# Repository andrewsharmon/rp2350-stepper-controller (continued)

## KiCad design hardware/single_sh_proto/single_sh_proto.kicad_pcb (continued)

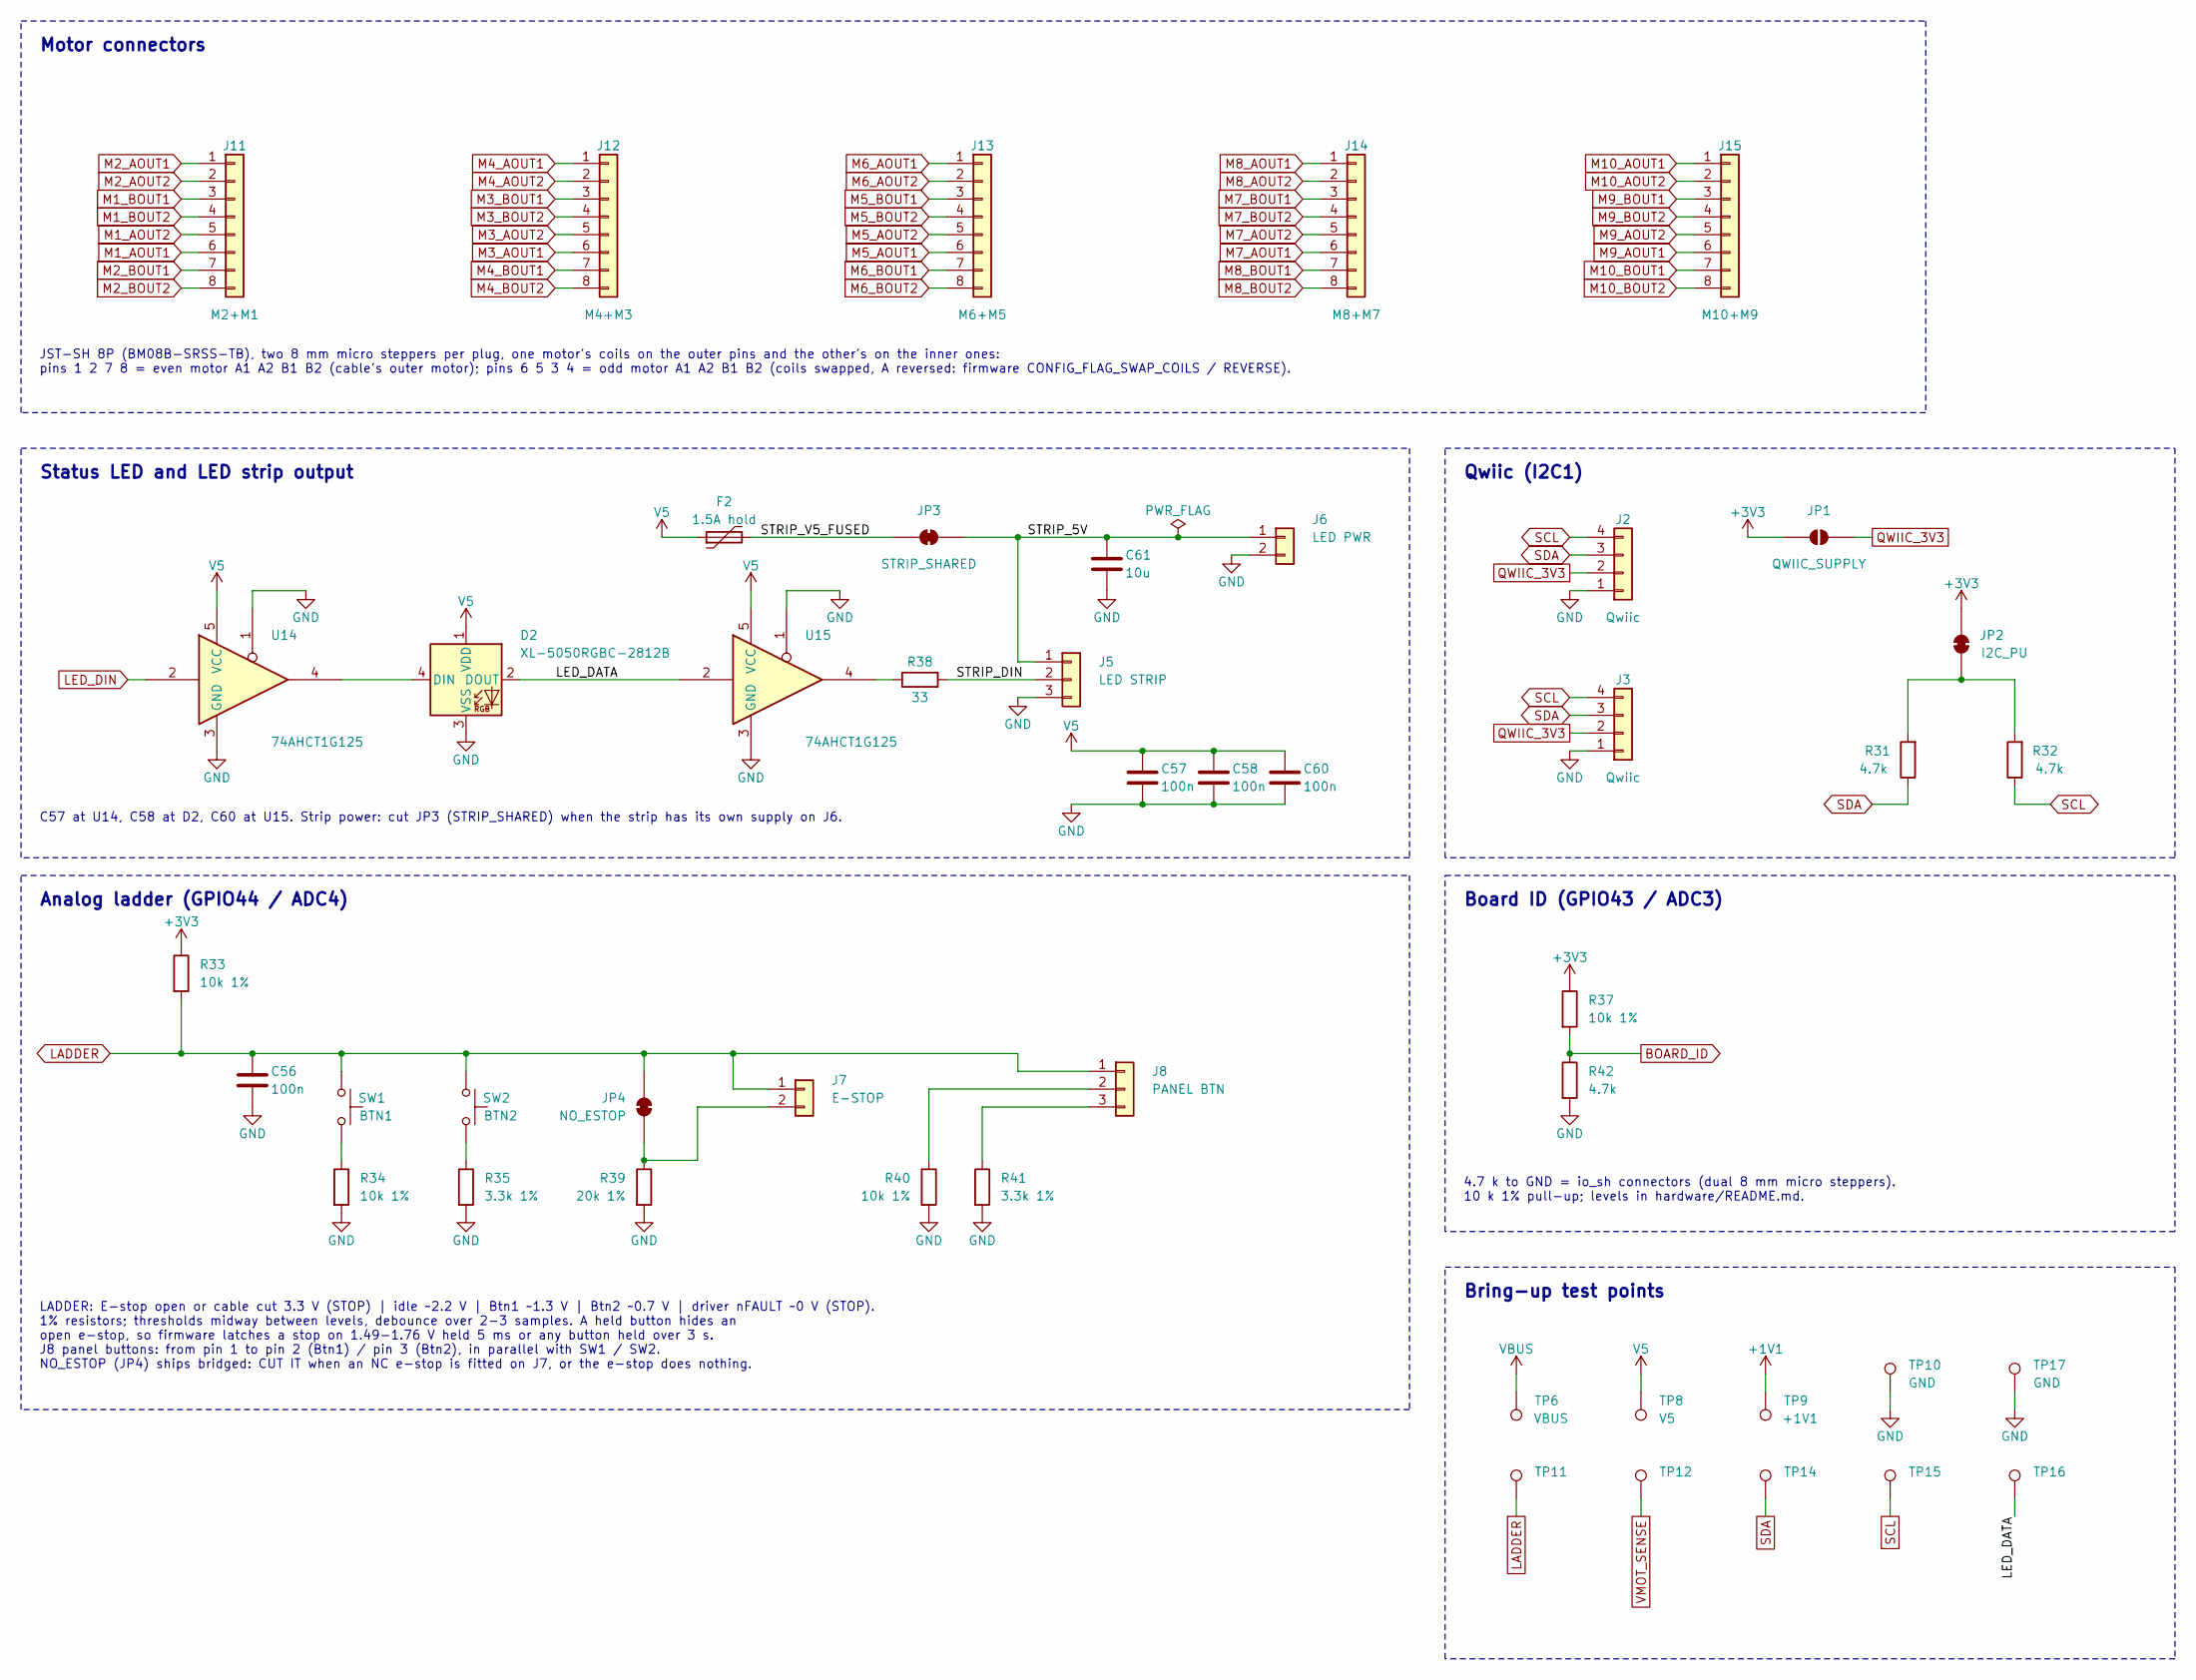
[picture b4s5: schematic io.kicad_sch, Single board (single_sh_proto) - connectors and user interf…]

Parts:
C56, C57, C58, C60: 100n; C_0603_1608Metric; MPN CC0603KRX7R9BB104; LCSC C14663
C61: 10u; C_0603_1608Metric; MPN CL10A106KP8NNNC; LCSC C19702
D2: XL-5050RGBC-2812B; LED_WS2812B_PLCC4_5.0x5.0mm_P3.2mm; MPN XL-5050RGBC-2812B; LCSC C2843785
F2: 1.5A hold; Fuse_1812_4532Metric; MPN SMD1812P150TF/8; LCSC C209721
J2, J3: Qwiic; JST_SH_BM04B-SRSS-TB_1x04-1MP_P1.00mm_Vertical; MPN BM04B-SRSS-TB; LCSC C160390
J5: LED STRIP; JST_XH_B3B-XH-A_1x03_P2.50mm_Vertical; MPN B3B-XH-A; LCSC C144394
J6: LED PWR; JST_PH_B2B-PH-K_1x02_P2.00mm_Vertical; MPN B2B-PH-K-S; LCSC C131337
J7: E-STOP; JST_PH_B2B-PH-K_1x02_P2.00mm_Vertical; MPN B2B-PH-K-S; LCSC C131337
J8: PANEL BTN; JST_PH_B3B-PH-K_1x03_P2.00mm_Vertical; MPN B3B-PH-K-S; LCSC C131339
J11: M2+M1; JST_SH_BM08B-SRSS-TB_1x08-1MP_P1.00mm_Vertical; MPN BM08B-SRSS-TB; LCSC C160394
J12: M4+M3; JST_SH_BM08B-SRSS-TB_1x08-1MP_P1.00mm_Vertical; MPN BM08B-SRSS-TB; LCSC C160394
J13: M6+M5; JST_SH_BM08B-SRSS-TB_1x08-1MP_P1.00mm_Vertical; MPN BM08B-SRSS-TB; LCSC C160394
J14: M8+M7; JST_SH_BM08B-SRSS-TB_1x08-1MP_P1.00mm_Vertical; MPN BM08B-SRSS-TB; LCSC C160394
J15: M10+M9; JST_SH_BM08B-SRSS-TB_1x08-1MP_P1.00mm_Vertical; MPN BM08B-SRSS-TB; LCSC C160394
JP1: QWIIC_SUPPLY; SolderJumper-2_P1.3mm_Open_RoundedPad1.0x1.5mm
JP2: I2C_PU; SolderJumper-2_P1.3mm_Bridged_RoundedPad1.0x1.5mm
JP3: STRIP_SHARED; SolderJumper-2_P1.3mm_Bridged_RoundedPad1.0x1.5mm
JP4: NO_ESTOP; SolderJumper-2_P1.3mm_Bridged_RoundedPad1.0x1.5mm
R31, R32, R42: 4.7k; R_0603_1608Metric; MPN 0603WAF4701T5E; LCSC C23162
R33, R34, R37, R40: 10k 1%; R_0603_1608Metric; MPN 0603WAF1002T5E; LCSC C25804
R35, R41: 3.3k 1%; R_0603_1608Metric; MPN 0603WAF3301T5E; LCSC C22978
R38: 33; R_0603_1608Metric; MPN 0603WAF330JT5E; LCSC C23140
R39: 20k 1%; R_0603_1608Metric; MPN 0603WAF2002T5E; LCSC C4184
SW1: BTN1; SW_SPST_TS-1088-xR020; MPN TS-1088-AR02016; LCSC C720477
SW2: BTN2; SW_SPST_TS-1088-xR020; MPN TS-1088-AR02016; LCSC C720477
TP6: VBUS; TestPoint_Pad_D1.0mm
TP8: V5; TestPoint_Pad_D1.0mm
TP9: +1V1; TestPoint_Pad_D1.0mm
TP10, TP17: GND; TestPoint_Pad_D1.0mm
TP11: LADDER; TestPoint_Pad_D1.0mm
TP12: VMOT_SENSE; TestPoint_Pad_D1.0mm
TP14: SDA; TestPoint_Pad_D1.0mm
TP15: SCL; TestPoint_Pad_D1.0mm
TP16: LED_DATA; TestPoint_Pad_D1.0mm
U14, U15: 74AHCT1G125; SOT-23-5; MPN SN74AHCT1G125DBVR; LCSC C7484

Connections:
+1V1: TP9.1; also elsewhere on the board
+3V3: JP1.1 (A), JP2.2 (B), R33.1, R37.1; also elsewhere on the board
/Connectors and UI/LED_DATA: D2.2 (DOUT), TP16.1, U15.2
/Connectors and UI/STRIP_5V: C61.1, J5.1, J6.1, JP3.2 (B)
/Connectors and UI/STRIP_DIN: J5.2, R38.2
/Connectors and UI/STRIP_V5_FUSED: F2.2, JP3.1 (A)
BOARD_ID: R37.2, R42.1; also elsewhere on the board
GND: C56.2, C57.2, C58.2, C60.2, C61.2, D2.3 (VSS), J2.1, J3.1, J5.3, J6.2, R34.2, R35.2, R39.2, R40.2, R41.2, R42.2, TP10.1, TP17.1, U14.1, U14.3 (GND), U15.1, U15.3 (GND); also elsewhere on the board
LADDER: C56.1, J7.1, J8.1, JP4.1 (A), R33.2, SW1.1, SW2.1, TP11.1; also elsewhere on the board
LED_DIN: U14.2; also elsewhere on the board
M1_AOUT1: J11.6; also elsewhere on the board
M1_AOUT2: J11.5; also elsewhere on the board
M1_BOUT1: J11.3; also elsewhere on the board
M1_BOUT2: J11.4; also elsewhere on the board
M2_AOUT1: J11.1; also elsewhere on the board
M2_AOUT2: J11.2; also elsewhere on the board
M2_BOUT1: J11.7; also elsewhere on the board
M2_BOUT2: J11.8; also elsewhere on the board
M3_AOUT1: J12.6; also elsewhere on the board
M3_AOUT2: J12.5; also elsewhere on the board
M3_BOUT1: J12.3; also elsewhere on the board
M3_BOUT2: J12.4; also elsewhere on the board
M4_AOUT1: J12.1; also elsewhere on the board
M4_AOUT2: J12.2; also elsewhere on the board
M4_BOUT1: J12.7; also elsewhere on the board
M4_BOUT2: J12.8; also elsewhere on the board
M5_AOUT1: J13.6; also elsewhere on the board
M5_AOUT2: J13.5; also elsewhere on the board
M5_BOUT1: J13.3; also elsewhere on the board
M5_BOUT2: J13.4; also elsewhere on the board
M6_AOUT1: J13.1; also elsewhere on the board
M6_AOUT2: J13.2; also elsewhere on the board
M6_BOUT1: J13.7; also elsewhere on the board
M6_BOUT2: J13.8; also elsewhere on the board
M7_AOUT1: J14.6; also elsewhere on the board
M7_AOUT2: J14.5; also elsewhere on the board
M7_BOUT1: J14.3; also elsewhere on the board
M7_BOUT2: J14.4; also elsewhere on the board
M8_AOUT1: J14.1; also elsewhere on the board
M8_AOUT2: J14.2; also elsewhere on the board
M8_BOUT1: J14.7; also elsewhere on the board
M8_BOUT2: J14.8; also elsewhere on the board
M9_AOUT1: J15.6; also elsewhere on the board
M9_AOUT2: J15.5; also elsewhere on the board
M9_BOUT1: J15.3; also elsewhere on the board
M9_BOUT2: J15.4; also elsewhere on the board
M10_AOUT1: J15.1; also elsewhere on the board
M10_AOUT2: J15.2; also elsewhere on the board
M10_BOUT1: J15.7; also elsewhere on the board
M10_BOUT2: J15.8; also elsewhere on the board
unnamed: D2.4 (DIN), U14.4
unnamed: J7.2, JP4.2 (B), R39.1
unnamed: J8.2, R40.1
unnamed: J8.3, R41.1
unnamed: JP2.1 (A), R31.2, R32.2
unnamed: R34.1, SW1.2
unnamed: R35.1, SW2.2
unnamed: R38.1, U15.4
QWIIC_3V3: J2.2, J3.2, JP1.2 (B)
SCL: J2.4, J3.4, R32.1, TP15.1; also elsewhere on the board
SDA: J2.3, J3.3, R31.1, TP14.1; also elsewhere on the board
V5: C57.1, C58.1, C60.1, D2.1 (VDD), F2.1, TP8.1, U14.5 (VCC), U15.5 (VCC); also elsewhere on the board
VBUS: TP6.1; also elsewhere on the board
VMOT_SENSE: TP12.1; also elsewhere on the board

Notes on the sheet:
Motor connectors
JST-SH 8P (BM08B-SRSS-TB), two 8 mm micro steppers per plug, one motor's coils on the outer pins and the other's on the inner ones: pins 1 2 7 8 = even motor A1 A2 B1 B2 (cable's outer motor); pins 6 5 3 4 = odd motor A1 A2 B1 B2 (coils swapped, A reversed: firmware CONFIG_FLAG_SWAP_COILS / REVERSE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
Status LED and LED strip output
C57 at U14, C58 at D2, C60 at U15. Strip power: cut JP3 (STRIP_SHARED) when the strip has its own supply on J6.
Qwiic (I2C1)
Analog ladder (GPIO44 / ADC4)
LADDER: E-stop open or cable cut 3.3 V (STOP) | idle ~2.2 V | Btn1 ~1.3 V | Btn2 ~0.7 V | driver nFAULT ~0 V (STOP). 1% resistors; thresholds midway between levels, debounce over 2-3 samples. A held button hides an open e-stop, so firmware latches a stop on 1.49-1.76 V held 5 ms or any button held 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
Board ID (GPIO43 / ADC3)
4.7 k to GND = io_sh connectors (dual 8 mm micro steppers). 10 k 1% pull-up; levels in hardware/README.md.
Bring-up test points

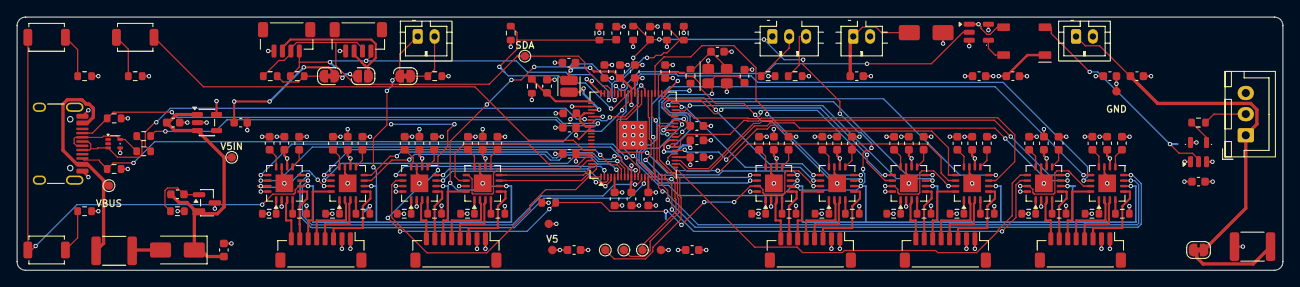
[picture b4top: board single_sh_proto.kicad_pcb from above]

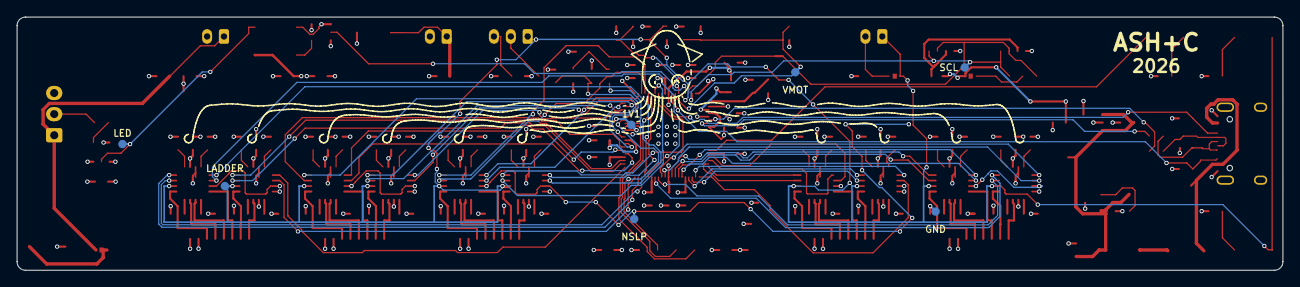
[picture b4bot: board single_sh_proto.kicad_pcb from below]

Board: 4 copper layers, 150.0 x 30.0 mm, 163 parts (7 on the bottom side), 165 nets.

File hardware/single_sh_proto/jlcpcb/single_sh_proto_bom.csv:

Comment,Designator,Footprint,LCSC Part #
1u,"C1,C4,C7,C10,C13,C16,C19,C22,C25,C28,C53,C55,C59",C_0603_1608Metric,C15849
100n,"C2,C5,C8,C11,C14,C17,C20,C23,C26,C29,C34,C35,C36,C37,C38,C39,C40,C41,C42,C43,C45,C46,C47,C54,C56,C57,C58,C60",C_0603_1608Metric,C14663
2.2u,"C3,C6,C9,C12,C15,C18,C21,C24,C27,C30",C_0603_1608Metric,C23630
10u,"C31,C32,C33,C52,C61",C_0603_1608Metric,C19702
4.7u,"C44,C48,C49",C_0603_1608Metric,C19666
15p,"C50,C51",C_0603_1608Metric,C1644
SS54,"D1,D3",D_SMA,C22452
XL-5050RGBC-2812B,D2,LED_WS2812B_PLCC4_5.0x5.0mm_P3.2mm,C2843785
1.5A hold,"F1,F2",Fuse_1812_4532Metric,C209721
USB-C,J1,USB_C_Receptacle_HRO_TYPE-C-31-M-12,C165948
Qwiic,"J2,J3",JST_SH_BM04B-SRSS-TB_1x04-1MP_P1.00mm_Vertical,C160390
5V IN / LED PWR / E-STOP,"J4,J6,J7",JST_PH_B2B-PH-K_1x02_P2.00mm_Vertical,C131337
LED STRIP,J5,JST_XH_B3B-XH-A_1x03_P2.50mm_Vertical,C144394
PANEL BTN,J8,JST_PH_B3B-PH-K_1x03_P2.00mm_Vertical,C131339
M2+M1 / M4+M3 / M6+M5 / M8+M7 / M10+M9,"J11,J12,J13,J14,J15",JST_SH_BM08B-SRSS-TB_1x08-1MP_P1.00mm_Vertical,C160394
3.3u,L1,L_Cenker_CKCS201610,C411344
AO3401A,Q1,SOT-23,C15127
1,"R1,R2,R3,R4,R5,R6,R7,R8,R9,R10,R11,R12,R13,R14,R15,R16,R17,R18,R19,R20",R_0603_1608Metric,C22936
47k,R21,R_0603_1608Metric,C25819
39k 1%,R22,R_0603_1608Metric,C23153
10k 1%,"R23,R33,R34,R37,R40",R_0603_1608Metric,C25804
33,"R24,R38",R_0603_1608Metric,C23140
1k,"R25,R36",R_0603_1608Metric,C21190
22,"R26,R27",R_0603_1608Metric,C23345
5.1k,"R28,R29",R_0603_1608Metric,C23186
100k,R30,R_0603_1608Metric,C25803
4.7k,"R31,R32,R42",R_0603_1608Metric,C23162
3.3k 1%,"R35,R41",R_0603_1608Metric,C22978
20k 1%,R39,R_0603_1608Metric,C4184
BTN1 / BTN2 / BOOTSEL,"SW1,SW2,SW3",SW_SPST_TS-1088-xR020,C720477
AT8833CQ,"U1,U2,U3,U4,U5,U6,U7,U8,U9,U10",QFN-16-1EP_4x4mm_P0.65mm_EP2.1x2.1mm,C5120769
RP2354B,U11,QFN-80-1EP_10x10mm_P0.4mm_EP3.4x3.4mm,C39843328
TPD2E2U06,U12,SOT-553,C1972959
ME6211C33M5G,U13,SOT-23-5,C82942
74AHCT1G125,"U14,U15",SOT-23-5,C7484
12MHz,Y1,Crystal_SMD_3225-4Pin_3.2x2.5mm,C20625731

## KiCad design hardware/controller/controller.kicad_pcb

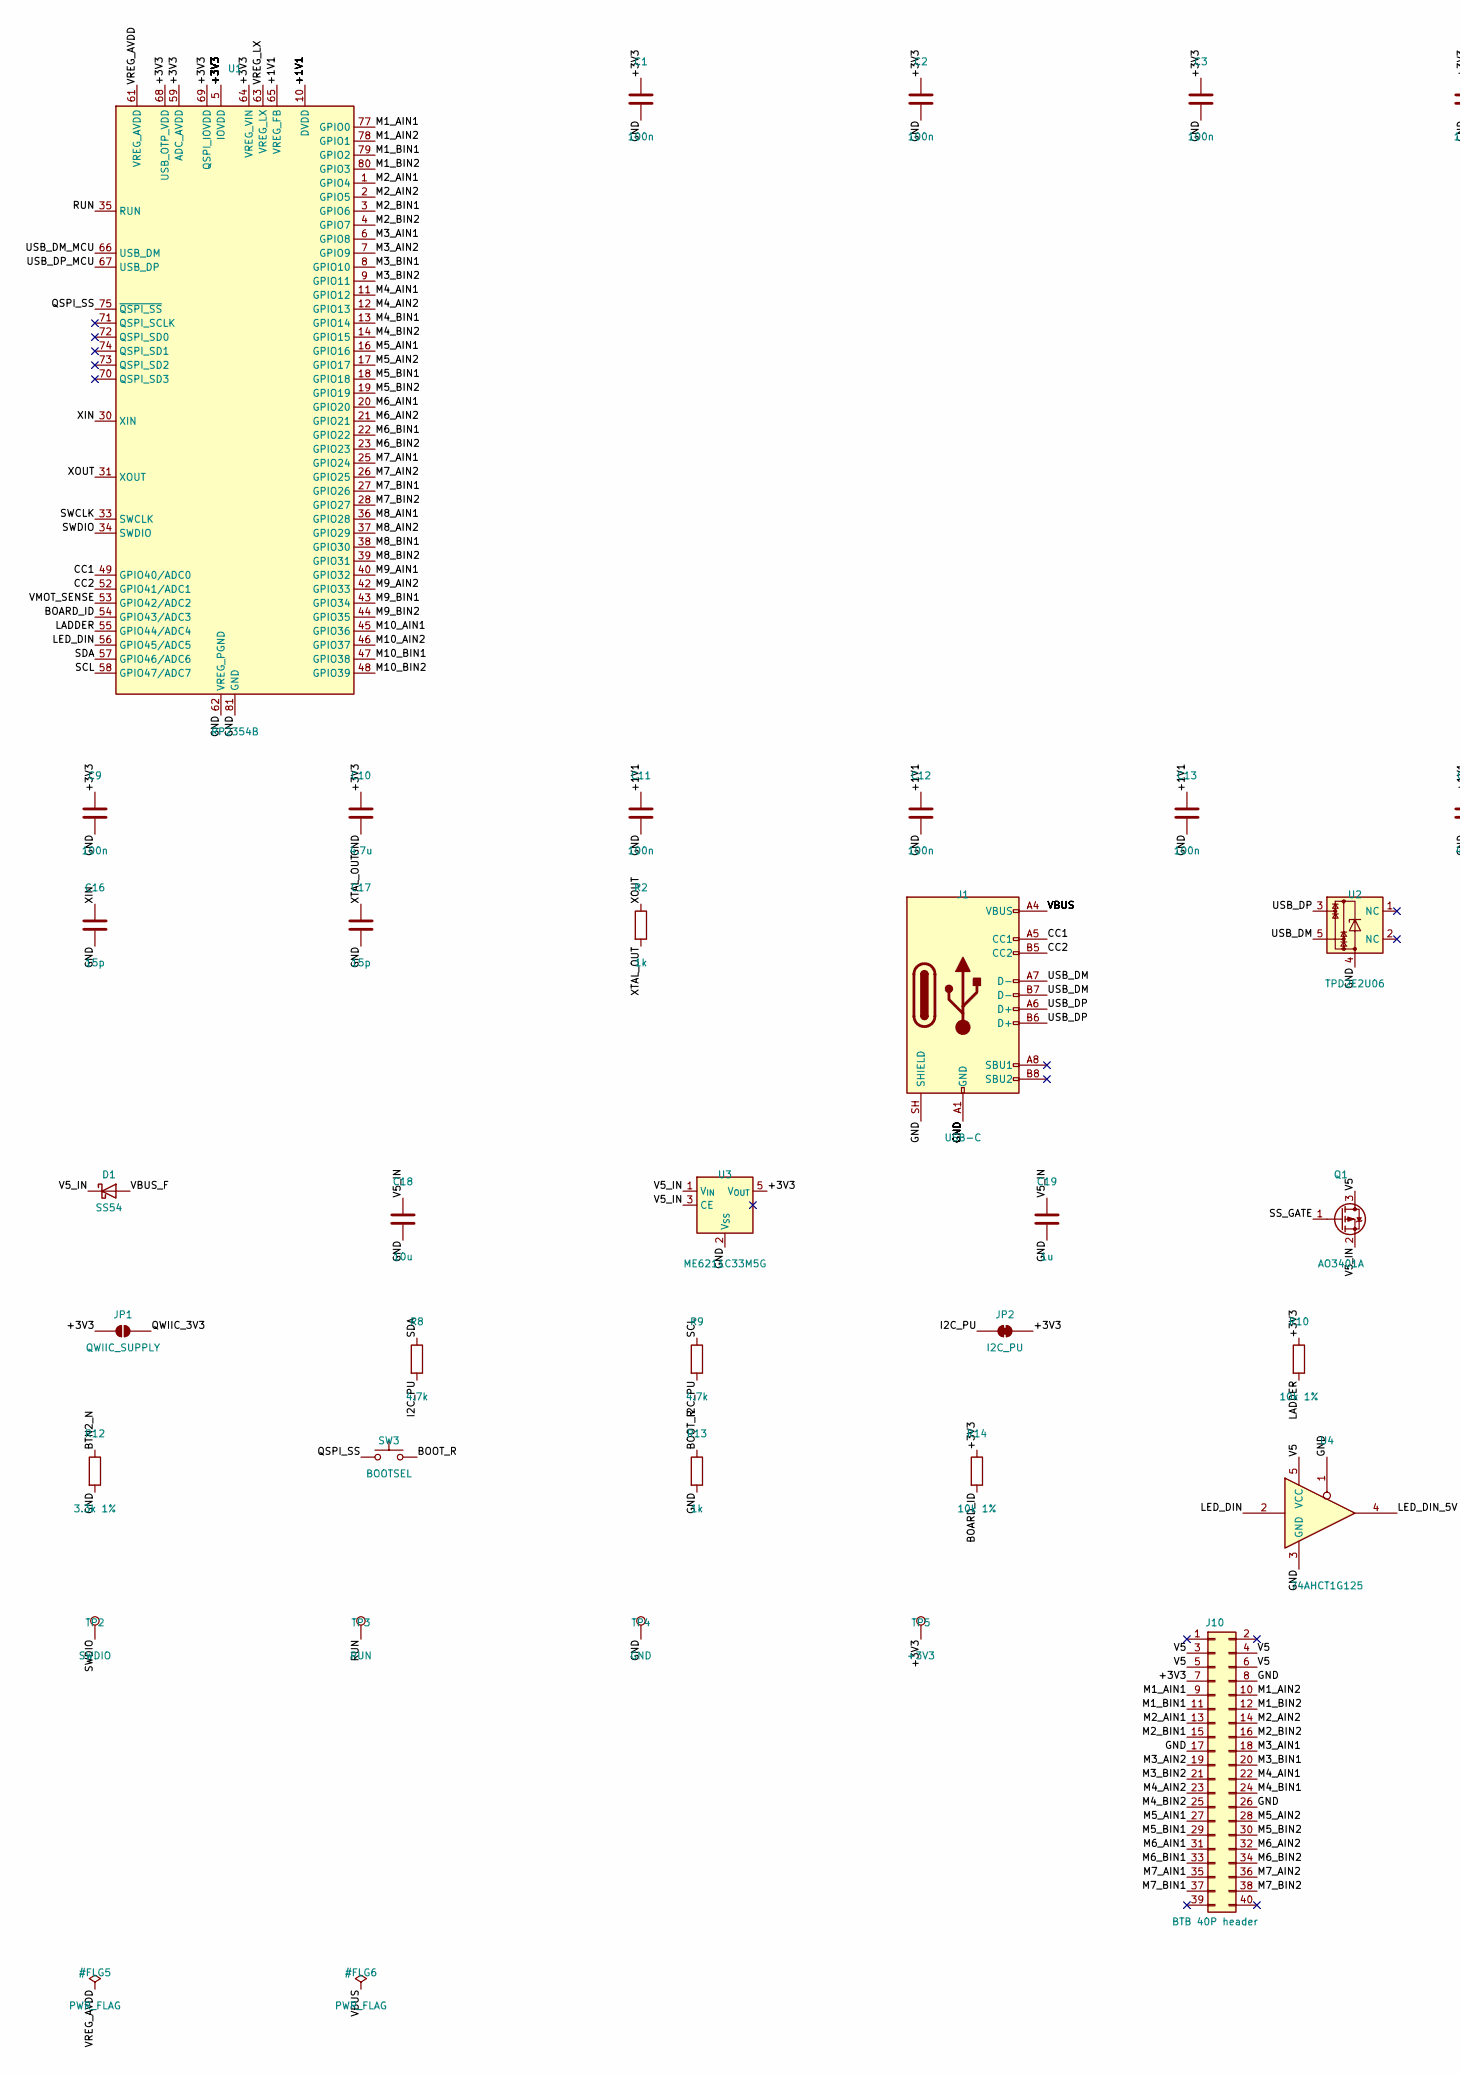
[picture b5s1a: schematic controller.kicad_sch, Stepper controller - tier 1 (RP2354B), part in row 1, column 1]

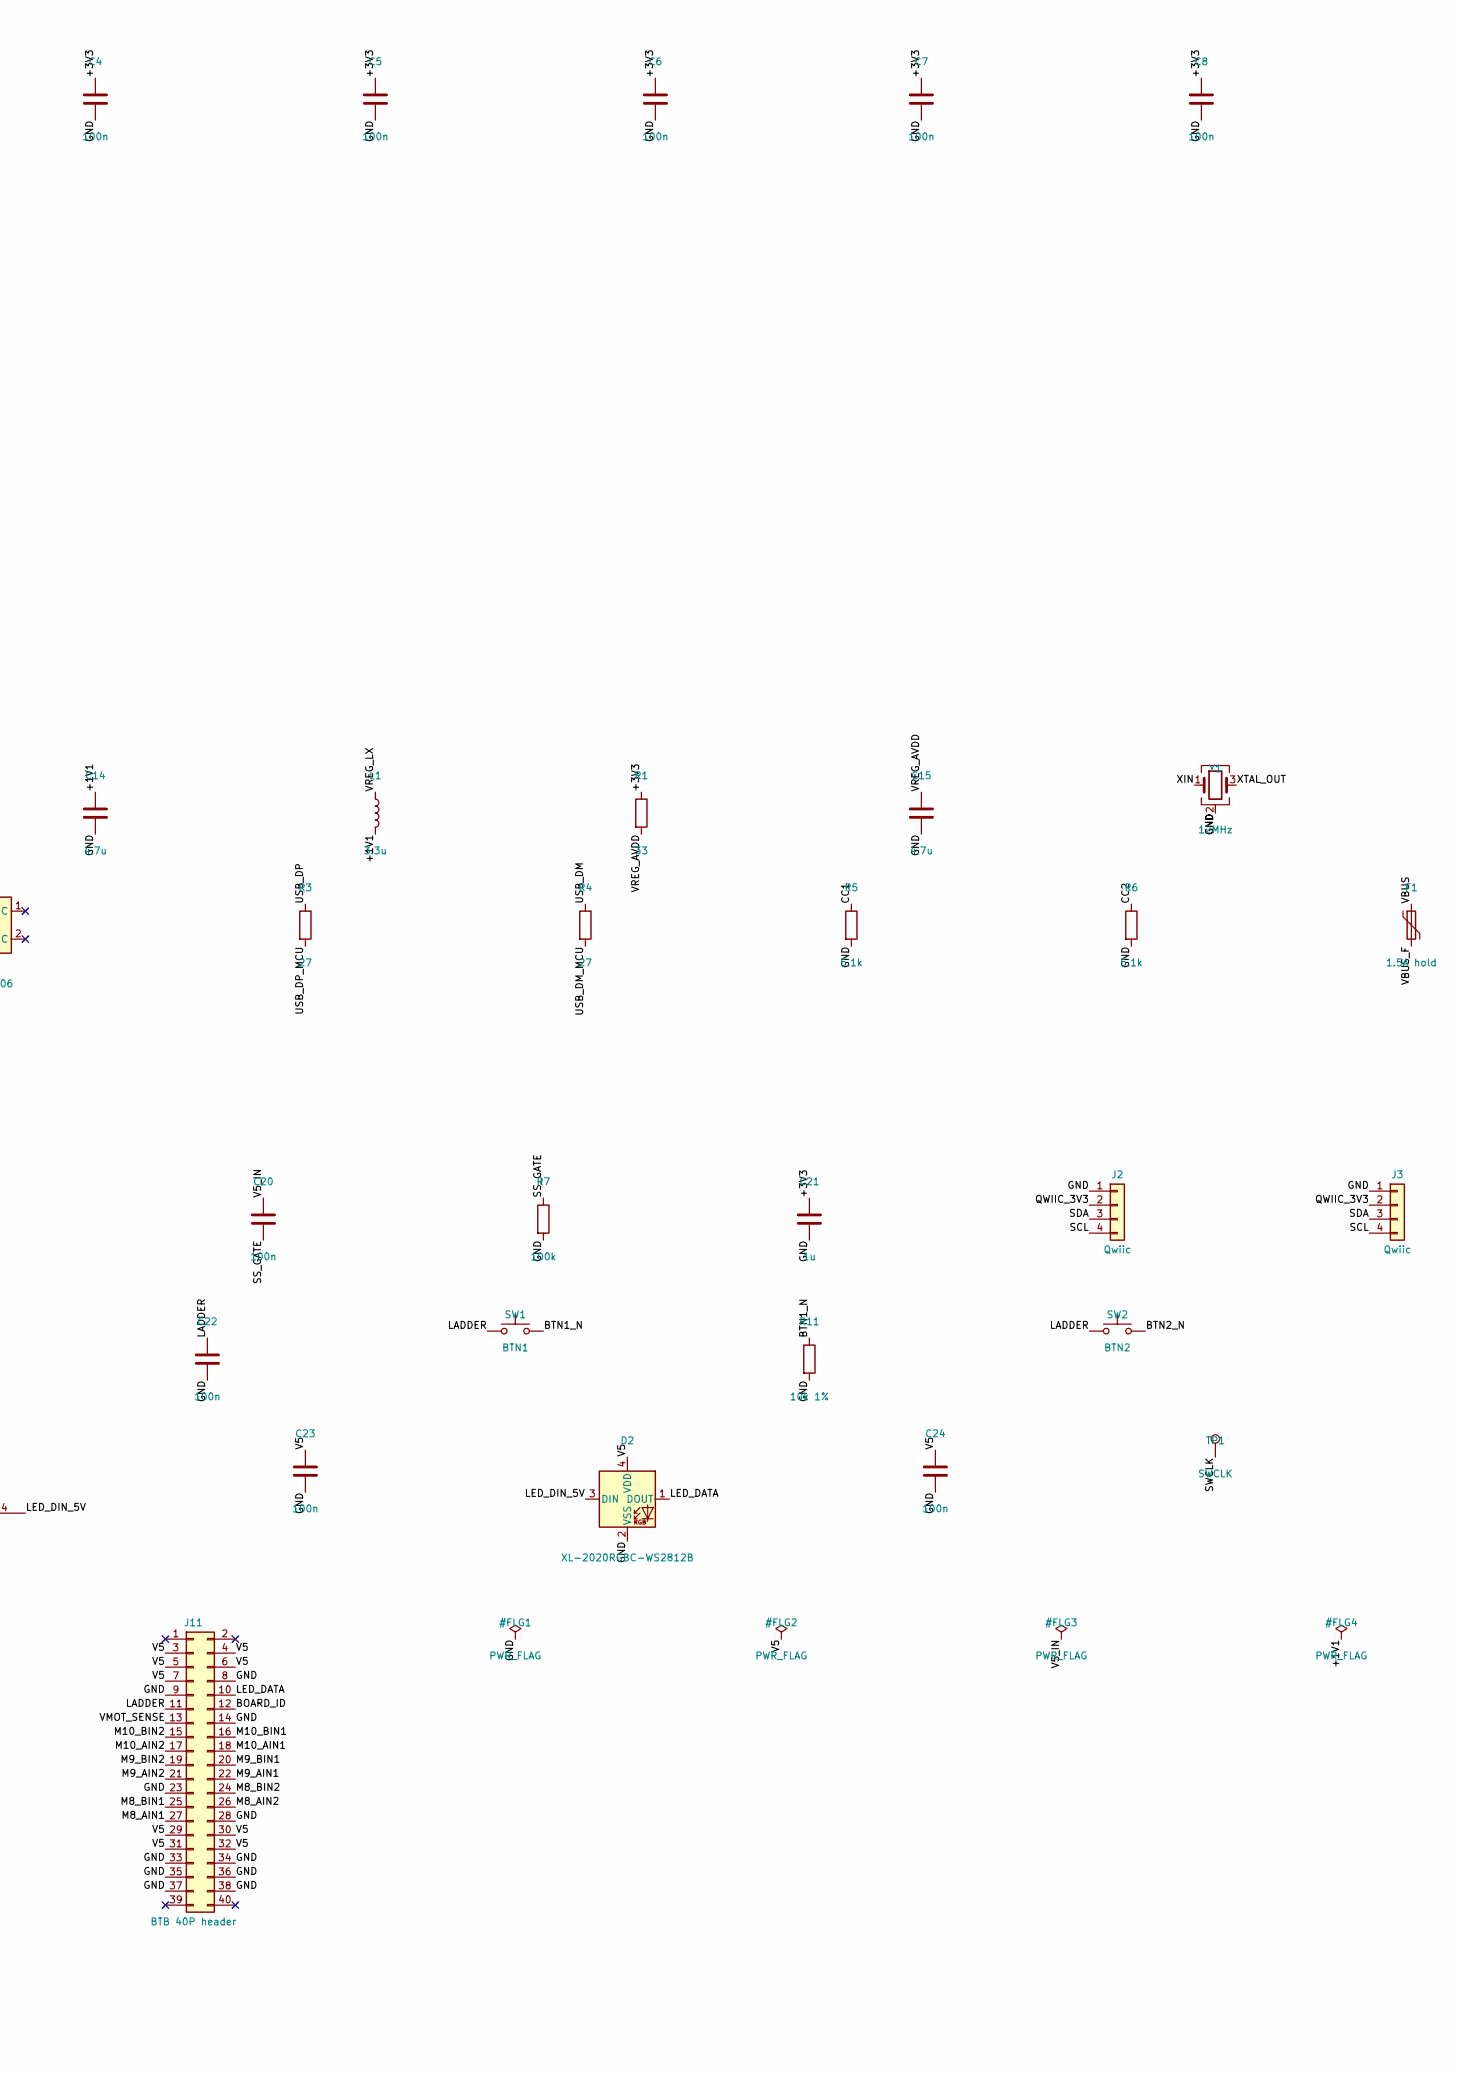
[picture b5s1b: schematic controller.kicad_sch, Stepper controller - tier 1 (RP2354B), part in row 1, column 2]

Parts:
C1, C2, C3, C4, C5, C6, C7, C8, C9, C11, C12, C13, C20, C22, C23, C24: 100n; C_0402_1005Metric; MPN CL05B104KO5NNNC; LCSC C1525
C10, C14, C15: 4.7u; C_0402_1005Metric; MPN CL05A475MP5NRNC; LCSC C23733
C16, C17: 15p; C_0402_1005Metric; MPN 0402CG150J500NT; LCSC C1548
C18: 10u; C_0805_2012Metric; MPN CL21A106KAYNNNE; LCSC C15850
C19, C21: 1u; C_0402_1005Metric; MPN CL05A105KA5NQNC; LCSC C52923
D1: SS54; D_SMA; MPN SS54; LCSC C22452
D2: XL-2020RGBC-WS2812B; LED_WS2812B-2020_PLCC4_2.0x2.0mm; MPN XL-2020RGBC-WS2812B; LCSC C5349955
F1: 1.5A hold; Fuse_1812_4532Metric; MPN SMD1812P150TF/8; LCSC C209721
J1: USB-C; USB_C_Receptacle_HRO_TYPE-C-31-M-12; MPN TYPE-C-31-M-12; LCSC C165948
J2, J3: Qwiic; JST_SH_BM04B-SRSS-TB_1x04-1MP_P1.00mm_Vertical; MPN BM04B-SRSS-TB; LCSC C160390
J10, J11: BTB 40P header; Hirose_DF40C-40DP_Header; MPN DF40C-40DP-0.4V(51); LCSC C424643
JP1: QWIIC_SUPPLY; SolderJumper-2_P1.3mm_Open_RoundedPad1.0x1.5mm
JP2: I2C_PU; SolderJumper-2_P1.3mm_Bridged_RoundedPad1.0x1.5mm
L1: 3.3u; L_Cenker_CKCS201610; MPN AOTA-B201610S3R3-101-T; LCSC C42411119
Q1: AO3401A; SOT-23; MPN AO3401A; LCSC C15127
R1: 33; R_0402_1005Metric; MPN 0402WGF330JTCE; LCSC C25105
R2, R13: 1k; R_0402_1005Metric; MPN 0402WGF1001TCE; LCSC C11702
R3, R4: 27; R_0402_1005Metric; MPN 0402WGF270JTCE; LCSC C25100
R5, R6: 5.1k; R_0402_1005Metric; MPN 0402WGF5101TCE; LCSC C25905
R7: 100k; R_0402_1005Metric; MPN 0402WGF1003TCE; LCSC C25741
R8, R9: 4.7k; R_0402_1005Metric; MPN 0402WGF4701TCE; LCSC C25900
R10, R11, R14: 10k 1%; R_0402_1005Metric; MPN 0402WGF1002TCE; LCSC C25744
R12: 3.3k 1%; R_0402_1005Metric; MPN 0402WGF3301TCE; LCSC C25890
SW1: BTN1; SW_SPST_TS-1088-xR020; MPN TS-1088-AR02016; LCSC C720477
SW2: BTN2; SW_SPST_TS-1088-xR020; MPN TS-1088-AR02016; LCSC C720477
SW3: BOOTSEL; SW_Push_1P1T_XKB_TS-1187A; MPN TS-1187A-B-A-B; LCSC C318884
TP1: SWCLK; TestPoint_Pad_D1.0mm
TP2: SWDIO; TestPoint_Pad_D1.0mm
TP3: RUN; TestPoint_Pad_D1.0mm
TP4: GND; TestPoint_Pad_D1.0mm
TP5: +3V3; TestPoint_Pad_D1.0mm
U1: RP2354B; QFN-80-1EP_10x10mm_P0.4mm_EP3.4x3.4mm; MPN RP2354B; LCSC C39843328
U2: TPD2E2U06; SOT-553; MPN TPD2E2U06DRLR; LCSC C1972959
U3: ME6211C33M5G; SOT-23-5; MPN ME6211C33M5G-N; LCSC C82942
U4: 74AHCT1G125; SOT-23-5; MPN SN74AHCT1G125DBVR; LCSC C7484
Y1: 12MHz; Crystal_SMD_3225-4Pin_3.2x2.5mm; MPN ABM8-272-T3; LCSC C20625731

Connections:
/+1V1: C11.1, C12.1, C13.1, C14.1, L1.2, U1.10 (DVDD), U1.32 (DVDD), U1.51 (DVDD), U1.65 (VREG_FB)
/+3V3: C1.1, C2.1, C3.1, C4.1, C5.1, C6.1, C7.1, C8.1, C9.1, C10.1, C21.1, J10.7, JP1.1 (A), JP2.2 (B), R1.1, R10.1, R14.1, TP5.1, U1.5 (IOVDD), U1.15 (IOVDD), U1.24 (IOVDD), U1.29 (IOVDD), U1.41 (IOVDD), U1.50 (IOVDD), U1.59 (ADC_AVDD), U1.60 (IOVDD), U1.64 (VREG_VIN), U1.68 (USB_OTP_VDD), U1.69 (QSPI_IOVDD), U1.76 (IOVDD), U3.5 (V_{OUT})
/BOARD_ID: J11.12, R14.2, U1.54 (GPIO43/ADC3)
/BOOT_R: R13.1, SW3.2
/BTN1_N: R11.1, SW1.2
/BTN2_N: R12.1, SW2.2
/CC1: J1.A5 (CC1), R5.1, U1.49 (GPIO40/ADC0)
/CC2: J1.B5 (CC2), R6.1, U1.52 (GPIO41/ADC1)
/GND: C1.2, C2.2, C3.2, C4.2, C5.2, C6.2, C7.2, C8.2, C9.2, C10.2, C11.2, C12.2, C13.2, C14.2, C15.2, C16.2, C17.2, C18.2, C19.2, C21.2, C22.2, C23.2, C24.2, D2.2 (VSS), J1.A1 (GND), J1.A12 (GND), J1.B1 (GND), J1.B12 (GND), J1.SH (SHIELD), J2.1, J3.1, J10.8, J10.17, J10.26, J11.8, J11.9, J11.14, J11.23, J11.28, J11.33, J11.34, J11.35, J11.36, J11.37, J11.38, R5.2, R6.2, R7.2, R11.2, R12.2, R13.2, TP4.1, U1.62 (VREG_PGND), U1.81 (GND), U2.4, U3.2 (V_{SS}), U4.1, U4.3 (GND), Y1.2 (G), Y1.4 (G)
/I2C_PU: JP2.1 (A), R8.2, R9.2
/LADDER: C22.1, J11.11, R10.2, SW1.1, SW2.1, U1.55 (GPIO44/ADC4)
/LED_DATA: D2.1 (DOUT), J11.10
/LED_DIN: U1.56 (GPIO45/ADC5), U4.2
/LED_DIN_5V: D2.3 (DIN), U4.4
/M1_AIN1: J10.9, U1.77 (GPIO0)
/M1_AIN2: J10.10, U1.78 (GPIO1)
/M1_BIN1: J10.11, U1.79 (GPIO2)
/M1_BIN2: J10.12, U1.80 (GPIO3)
/M2_AIN1: J10.13, U1.1 (GPIO4)
/M2_AIN2: J10.14, U1.2 (GPIO5)
/M2_BIN1: J10.15, U1.3 (GPIO6)
/M2_BIN2: J10.16, U1.4 (GPIO7)
/M3_AIN1: J10.18, U1.6 (GPIO8)
/M3_AIN2: J10.19, U1.7 (GPIO9)
/M3_BIN1: J10.20, U1.8 (GPIO10)
/M3_BIN2: J10.21, U1.9 (GPIO11)
/M4_AIN1: J10.22, U1.11 (GPIO12)
/M4_AIN2: J10.23, U1.12 (GPIO13)
/M4_BIN1: J10.24, U1.13 (GPIO14)
/M4_BIN2: J10.25, U1.14 (GPIO15)
/M5_AIN1: J10.27, U1.16 (GPIO16)
/M5_AIN2: J10.28, U1.17 (GPIO17)
/M5_BIN1: J10.29, U1.18 (GPIO18)
/M5_BIN2: J10.30, U1.19 (GPIO19)
/M6_AIN1: J10.31, U1.20 (GPIO20)
/M6_AIN2: J10.32, U1.21 (GPIO21)
/M6_BIN1: J10.33, U1.22 (GPIO22)
/M6_BIN2: J10.34, U1.23 (GPIO23)
/M7_AIN1: J10.35, U1.25 (GPIO24)
/M7_AIN2: J10.36, U1.26 (GPIO25)
/M7_BIN1: J10.37, U1.27 (GPIO26)
/M7_BIN2: J10.38, U1.28 (GPIO27)
/M8_AIN1: J11.27, U1.36 (GPIO28)
/M8_AIN2: J11.26, U1.37 (GPIO29)
/M8_BIN1: J11.25, U1.38 (GPIO30)
/M8_BIN2: J11.24, U1.39 (GPIO31)
/M9_AIN1: J11.22, U1.40 (GPIO32)
/M9_AIN2: J11.21, U1.42 (GPIO33)
/M9_BIN1: J11.20, U1.43 (GPIO34)
/M9_BIN2: J11.19, U1.44 (GPIO35)
/M10_AIN1: J11.18, U1.45 (GPIO36)
/M10_AIN2: J11.17, U1.46 (GPIO37)
/M10_BIN1: J11.16, U1.47 (GPIO38)
/M10_BIN2: J11.15, U1.48 (GPIO39)
/QSPI_SS: SW3.1, U1.75 (~QSPI_SS)
/QWIIC_3V3: J2.2, J3.2, JP1.2 (B)
/RUN: TP3.1, U1.35 (RUN)
/SCL: J2.4, J3.4, R9.1, U1.58 (GPIO47/ADC7)
/SDA: J2.3, J3.3, R8.1, U1.57 (GPIO46/ADC6)
/SS_GATE: C20.2, Q1.1 (G), R7.1
/SWCLK: TP1.1, U1.33 (SWCLK)
/SWDIO: TP2.1, U1.34 (SWDIO)
/USB_DM: J1.A7 (D-), J1.B7 (D-), R4.1, U2.5
/USB_DM_MCU: R4.2, U1.66 (USB_DM)
/USB_DP: J1.A6 (D+), J1.B6 (D+), R3.1, U2.3
/USB_DP_MCU: R3.2, U1.67 (USB_DP)
/V5: C23.1, C24.1, D2.4 (VDD), J10.3, J10.4, J10.5, J10.6, J11.3, J11.4, J11.5, J11.6, J11.7, J11.29, J11.30, J11.31, J11.32, Q1.3 (D), U4.5 (VCC)
/V5_IN: C18.1, C19.1, C20.1, D1.1 (K), Q1.2 (S), U3.1 (V_{IN}), U3.3 (CE)
/VBUS: F1.1, J1.A4 (VBUS), J1.A9 (VBUS), J1.B4 (VBUS), J1.B9 (VBUS)
/VBUS_F: D1.2 (A), F1.2
/VMOT_SENSE: J11.13, U1.53 (GPIO42/ADC2)
/VREG_AVDD: C15.1, R1.2, U1.61 (VREG_AVDD)
/VREG_LX: L1.1, U1.63 (VREG_LX)
/XIN: C16.1, U1.30 (XIN), Y1.1
/XOUT: R2.1, U1.31 (XOUT)
/XTAL_OUT: C17.1, R2.2, Y1.3

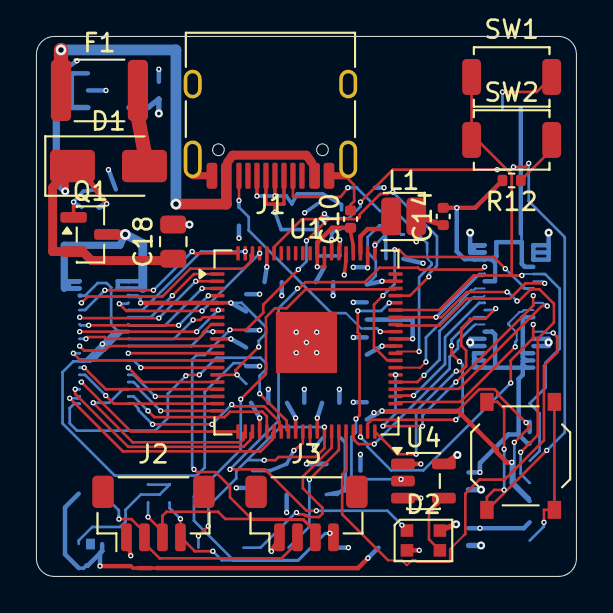
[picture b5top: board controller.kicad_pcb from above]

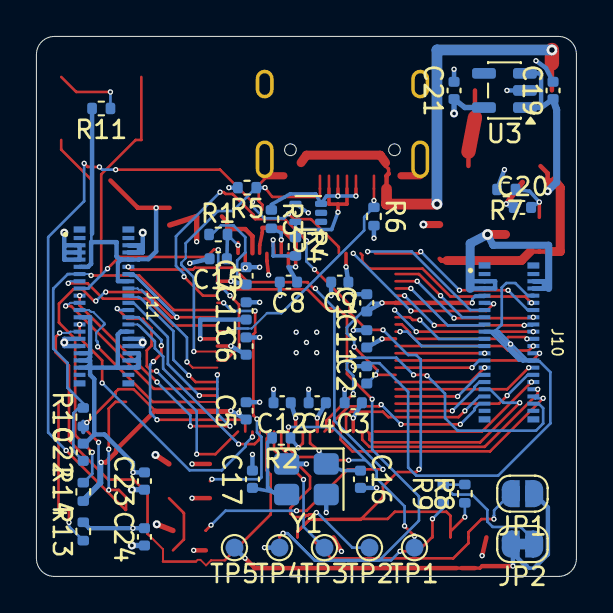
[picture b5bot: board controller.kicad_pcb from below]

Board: 4 copper layers, 30.0 x 30.0 mm, 63 parts (46 on the bottom side), 76 nets.

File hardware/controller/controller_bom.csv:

"Refs","Value","Footprint","Qty","MPN","LCSC","Note"
"C1,C2,C3,C4,C5,C6,C7,C8,C9,C11,C12,C13,C22,C23,C24","100n","Capacitor_SMD:C_0402_1005Metric","15","CL05B104KO5NNNC","C1525",""
"C10,C14,C15","4.7u","Capacitor_SMD:C_0402_1005Metric","3","CL05A475MP5NRNC","C23733",""
"C16,C17","15p","Capacitor_SMD:C_0402_1005Metric","2","0402CG150J500NT","C1548",""
"C18","10u","Capacitor_SMD:C_0805_2012Metric","1","CL21A106KAYNNNE","C15850",""
"C19,C21","1u","Capacitor_SMD:C_0402_1005Metric","2","CL05A105KA5NQNC","C52923",""
"C20","100n","Capacitor_SMD:C_0402_1005Metric","1","CL05B104KO5NNNC","C1525","soft-start timing with the 100k"
"D1","SS54","Diode_SMD:D_SMA","1","SS54","C22452","MDD; Vf 0.55 V @ 5 A"
"D2","XL-2020RGBC-WS2812B","LED_SMD:LED_WS2812B-2020_PLCC4_2.0x2.0mm","1","XL-2020RGBC-WS2812B","C5349955","XINGLIGHT; WS2812B-2020 pinout and footprint; Worldsemi C965555 was out of stock at JLCPCB"
"F1","1.5A hold","Fuse:Fuse_1812_4532Metric","1","SMD1812P150TF/8","C209721","PTTC; 1.5 A hold / 3 A trip, 8 V; alt C21002"
"J1","USB-C","Connector_USB:USB_C_Receptacle_HRO_TYPE-C-31-M-12","1","TYPE-C-31-M-12","C165948","THT shell legs; enclosure supports receptacle"
"J2,J3","Qwiic","Connector_JST:JST_SH_BM04B-SRSS-TB_1x04-1MP_P1.00mm_Vertical","2","BM04B-SRSS-TB","C160390",""
"J10","BTB 40P header","stack:Hirose_DF40C-40DP_Header","1","DF40C-40DP-0.4V(51)","C424643","connector A, board underside"
"J11","BTB 40P header","stack:Hirose_DF40C-40DP_Header","1","DF40C-40DP-0.4V(51)","C424643","connector B, board underside; offset placement keys stack"
"L1","3.3u","Inductor_SMD:L_Cenker_CKCS201610","1","AOTA-B201610S3R3-101-T","C42411119","Abracon part per RP2350 design guide; 2016 size"
"Q1","AO3401A","Package_TO_SOT_SMD:SOT-23","1","AO3401A","C15127","AOS; 60 mohm @ 4.5 V, Vth ~0.9 V"
"R1","33","Resistor_SMD:R_0402_1005Metric","1","0402WGF330JTCE","C25105",""
"R2,R13","1k","Resistor_SMD:R_0402_1005Metric","2","0402WGF1001TCE","C11702",""
"R3,R4","27","Resistor_SMD:R_0402_1005Metric","2","0402WGF270JTCE","C25100",""
"R5,R6","5.1k","Resistor_SMD:R_0402_1005Metric","2","0402WGF5101TCE","C25905",""
"R7","100k","Resistor_SMD:R_0402_1005Metric","1","0402WGF1003TCE","C25741","soft-start timing with the 100n"
"R8,R9","4.7k","Resistor_SMD:R_0402_1005Metric","2","0402WGF4701TCE","C25900",""
"R10,R11,R14","10k 1%","Resistor_SMD:R_0402_1005Metric","3","0402WGF1002TCE","C25744",""
"R12","3.3k 1%","Resistor_SMD:R_0402_1005Metric","1","0402WGF3301TCE","C25890",""
"SW1","BTN1","Button_Switch_SMD:SW_SPST_TS-1088-xR020","1","TS-1088-AR02016","C720477","XUNPU 3.9x3.0 mm 2-pad; small so the BTB fan-out routes"
"SW2","BTN2","Button_Switch_SMD:SW_SPST_TS-1088-xR020","1","TS-1088-AR02016","C720477","XUNPU 3.9x3.0 mm 2-pad; small so the BTB fan-out routes"
"SW3","BOOTSEL","Button_Switch_SMD:SW_Push_1P1T_XKB_TS-1187A","1","TS-1187A-B-A-B","C318884",""
"U1","RP2354B","Package_DFN_QFN:QFN-80-1EP_10x10mm_P0.4mm_EP3.4x3.4mm","1","RP2354B","C39843328","2 MB in-package flash; leave QSPI_SD0-3/SCLK unconnected"
"U2","TPD2E2U06","Package_TO_SOT_SMD:SOT-553","1","TPD2E2U06DRLR","C1972959","TI; 1.5 pF; pins 1-2 NC"
"U3","ME6211C33M5G","Package_TO_SOT_SMD:SOT-23-5","1","ME6211C33M5G-N","C82942",""
"U4","74AHCT1G125","Package_TO_SOT_SMD:SOT-23-5","1","SN74AHCT1G125DBVR","C7484",""
"Y1","12MHz","Crystal:Crystal_SMD_3225-4Pin_3.2x2.5mm","1","ABM8-272-T3","C20625731","Abracon, per RP2350 design guide; other crystals need retuning and testing"

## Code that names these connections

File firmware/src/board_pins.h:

#pragma once

// Application pin map. Motors always sit on GPIO 4*n..4*n+3; boards with
// fewer GPIOs run the remaining motors without pins.

#include "pico.h"

#define ADC_NONE 0xffu

#if NUM_BANK0_GPIOS > 32
// RP2354B stepper controller (hardware/README.md).
#define BOARD_MOTORS_WITH_PINS 10
#define BOARD_CC1_GPIO        40
#define BOARD_CC2_GPIO        41
#define BOARD_VMOT_GPIO       42
#ifdef BOARD_SINGLE_SH_PROTO
#define BOARD_VMOT_RATIO      4.9f   // 39k / 10k divider
#else
#define BOARD_VMOT_RATIO      5.0f   // 1:5 divider
#endif
#define BOARD_ID_GPIO         43
#define BOARD_LADDER_GPIO     44
#define BOARD_WS2812_GPIO     45
// Qwiic: I2C1 target (hardware/README.md). External pull-ups (RP2350-E9).
#define BOARD_I2C_SDA_GPIO    46
#define BOARD_I2C_SCL_GPIO    47
#define BOARD_I2C_TARGET_ADDR 0x42
#ifdef BOARD_SINGLE_SH_PROTO
// Axes in row order along the motor connectors, from the far end to the
// USB end: J13 M5 M6, J14 M7 M8, J15 M9 M10, J11 M1 M2, J12 M3 M4. The ToF
// map (tof_overlay.c) and the built-in programs (player.c) lay the axes
// out in this order.
#define BOARD_AXIS_ROW {4, 5, 6, 7, 8, 9, 0, 1, 2, 3}
#endif
#else
// Pico 2 bench (RP2350A, GPIO 0-29). Motors 1-5 on GPIO 0-19. The ladder and
// board ID go on the ADC header pins; VSYS/3 stands in for VMOTOR_SENSE.
// No free pins for the I2C target, so it is compiled out.
#define BOARD_MOTORS_WITH_PINS 5
#define BOARD_CC1_GPIO        ADC_NONE
#define BOARD_CC2_GPIO        ADC_NONE
#define BOARD_VMOT_GPIO       29
#define BOARD_VMOT_RATIO      3.0f   // Pico 2 VSYS/3 divider
#define BOARD_ID_GPIO         28
#define BOARD_LADDER_GPIO     26
#define BOARD_WS2812_GPIO     20
#endif

// Place of `axis` (0-based) along the row of actuators, counting only axes
// below `n`: its position in BOARD_AXIS_ROW, or the axis itself without one.
static inline int board_row_slot(int axis, int n) {
#ifdef BOARD_AXIS_ROW
    static const unsigned char row[] = BOARD_AXIS_ROW;
    int slot = 0;
    for (unsigned k = 0; k < sizeof row; k++) {
        if (row[k] == axis)
            return slot;
        if (row[k] < n)
            slot++;
    }
#else
    (void)n;
#endif
    return axis;
}
